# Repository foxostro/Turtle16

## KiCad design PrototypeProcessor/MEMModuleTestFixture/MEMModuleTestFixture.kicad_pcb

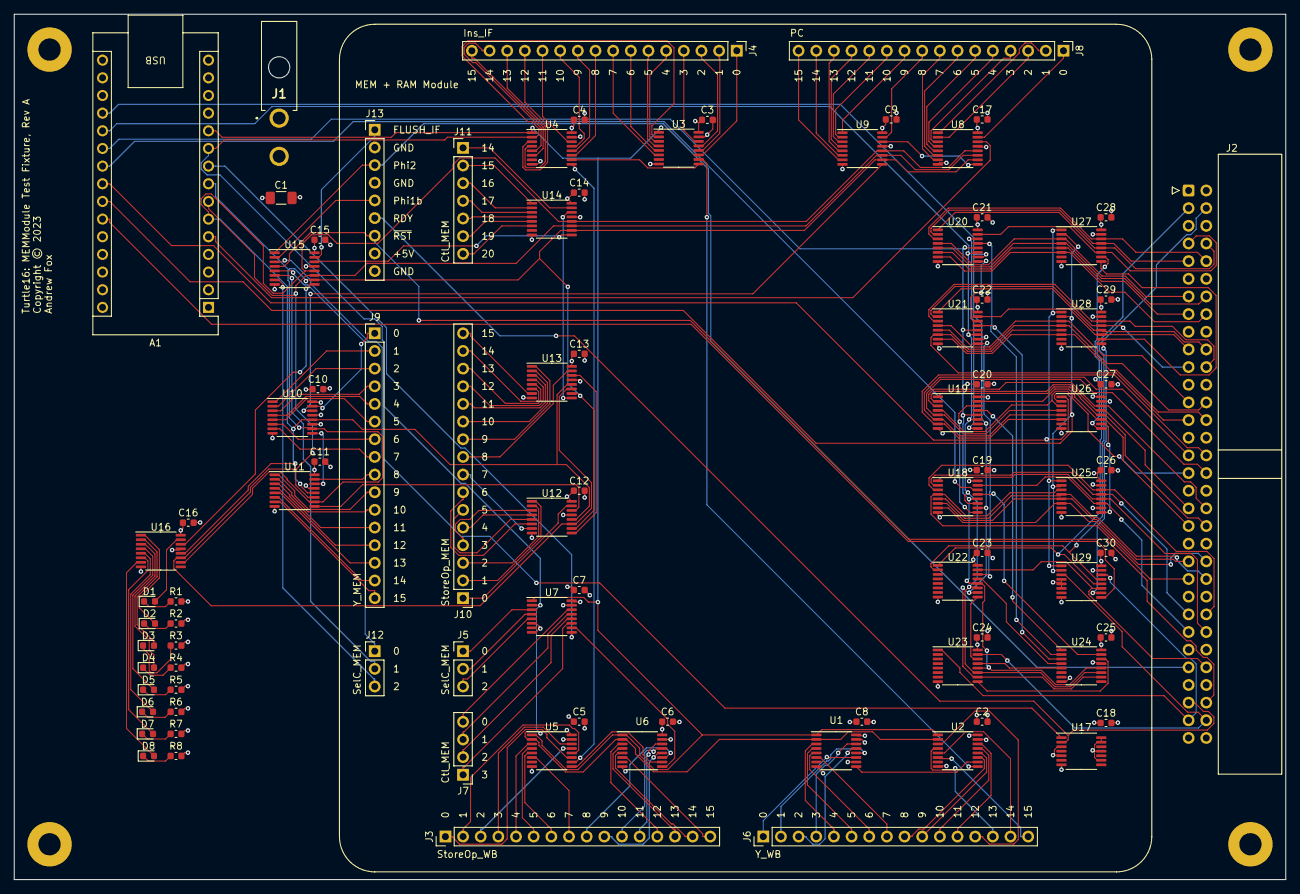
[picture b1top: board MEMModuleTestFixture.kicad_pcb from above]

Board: 4 copper layers, 182.9 x 124.5 mm, 93 parts (0 on the bottom side), 218 nets.

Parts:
A1: Arduino_Nano_Every; Arduino_Nano
C1: 100µF; C_1206_3216Metric_Pad1.33x1.80mm_HandSolder
C2, C3, C4, C5, C6, C7, C8, C9, C10, C11, C12, C13, C14, C15, C16, C17, C18, C19, C20, C21, C22, C23, C24, C25, C26, C27, C28, C29, C30: 0.1µF; C_0603_1608Metric
D1, D2, D3, D4, D5, D6, D7, D8: Red; LED_0603_1608Metric
H1, H2, H3, H4: MountingHole_Pad; MountingHole_3.2mm_M3_Pad
J1: Power; 172448-0002
J2: 71922-164LF; IDC-Header_2x32_P2.54mm_Horizontal
J3: StoreOp_WB; PinHeader_1x16_P2.54mm_Vertical
J4: Ins_IF; PinHeader_1x16_P2.54mm_Vertical
J5, J12: SelC_MEM; PinHeader_1x03_P2.54mm_Vertical
J6: Y_WB; PinHeader_1x16_P2.54mm_Vertical
J7: Ctl_MEM; PinHeader_1x04_P2.54mm_Vertical
J8: PC; PinHeader_1x16_P2.54mm_Vertical
J9: Y_MEM; PinHeader_1x16_P2.54mm_Vertical
J10: StoreOp_MEM; PinHeader_1x16_P2.54mm_Vertical
J11: Ctl_MEM; PinHeader_1x07_P2.54mm_Vertical
J13: Control Signals; PinHeader_1x09_P2.54mm_Vertical
R1, R2, R3, R4, R5, R6, R7, R8: 270R; C_0603_1608Metric
U1, U2, U3, U4, U5, U6, U7, U25, U26, U27, U28, U29: 74HC165; TSSOP-16_4.4x5mm_P0.65mm
U8, U9, U10, U11, U12, U13, U14, U15, U16, U18, U19, U20, U21, U22, U23, U24: 74HC595; TSSOP-16_4.4x5mm_P0.65mm
U17: 74HCT05; TSSOP-14_4.4x5mm_P0.65mm

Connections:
/Ctl_MEM14: J11.1, U14.15 (QA)
/Ctl_MEM15: J11.2, U14.1 (QB)
/Ctl_MEM16: J11.3, U14.2 (QC)
/Ctl_MEM17: J11.4, U14.3 (QD)
/Ctl_MEM18: J11.5, U14.4 (QE)
/Ctl_MEM19: J11.6, U14.5 (QF)
/Ctl_MEM20: J11.7, U14.6 (QG)
/Ctl_WB17: J7.1, U7.11 (D0)
/Ctl_WB18: J7.2, U7.12 (D1)
/Ctl_WB19: J7.3, U7.13 (D2)
/Ctl_WB20: J7.4, U7.14 (D3)
/Ins_IF0: J4.1, U3.11 (D0)
/Ins_IF1: J4.2, U3.12 (D1)
/Ins_IF2: J4.3, U3.13 (D2)
/Ins_IF3: J4.4, U3.14 (D3)
/Ins_IF4: J4.5, U3.3 (D4)
/Ins_IF5: J4.6, U3.4 (D5)
/Ins_IF6: J4.7, U3.5 (D6)
/Ins_IF7: J4.8, U3.6 (D7)
/Ins_IF8: J4.9, U4.11 (D0)
/Ins_IF9: J4.10, U4.12 (D1)
/Ins_IF10: J4.11, U4.13 (D2)
/Ins_IF11: J4.12, U4.14 (D3)
/Ins_IF12: J4.13, U4.3 (D4)
/Ins_IF13: J4.14, U4.4 (D5)
/Ins_IF14: J4.15, U4.5 (D6)
/Ins_IF15: J4.16, U4.6 (D7)
/MEM Prototype Inputs/FLUSH_IF: J13.1, U15.15 (QA)
/MEM Prototype Inputs/PC0: J8.1, U8.15 (QA)
/MEM Prototype Inputs/PC1: J8.2, U8.1 (QB)
/MEM Prototype Inputs/PC2: J8.3, U8.2 (QC)
/MEM Prototype Inputs/PC3: J8.4, U8.3 (QD)
/MEM Prototype Inputs/PC4: J8.5, U8.4 (QE)
/MEM Prototype Inputs/PC5: J8.6, U8.5 (QF)
/MEM Prototype Inputs/PC6: J8.7, U8.6 (QG)
/MEM Prototype Inputs/PC7: J8.8, U8.7 (QH)
/MEM Prototype Inputs/PC8: J8.9, U9.15 (QA)
/MEM Prototype Inputs/PC9: J8.10, U9.1 (QB)
/MEM Prototype Inputs/PC10: J8.11, U9.2 (QC)
/MEM Prototype Inputs/PC11: J8.12, U9.3 (QD)
/MEM Prototype Inputs/PC12: J8.13, U9.4 (QE)
/MEM Prototype Inputs/PC13: J8.14, U9.5 (QF)
/MEM Prototype Inputs/PC14: J8.15, U9.6 (QG)
/MEM Prototype Inputs/PC15: J8.16, U9.7 (QH)
/MEM Prototype Inputs/Phi1b: J13.5, U15.2 (QC)
/MEM Prototype Inputs/Phi2: J2.55, J13.3, U15.1 (QB)
/MEM Prototype Inputs/RDY: J2.59, J13.6, U17.2
/MEM Prototype Inputs/~RST_sync: J2.60, J13.7, U15.4 (QE)
/SelC_MEM0: J12.1, U15.5 (QF)
/SelC_MEM1: J12.2, U15.6 (QG)
/SelC_MEM2: J12.3, U15.7 (QH)
/SelC_WB0: J5.1, U7.3 (D4)
/SelC_WB1: J5.2, U7.4 (D5)
/SelC_WB2: J5.3, U7.5 (D6)
/StoreOp_MEM0: J10.1, U12.15 (QA)
/StoreOp_MEM1: J10.2, U12.1 (QB)
/StoreOp_MEM2: J10.3, U12.2 (QC)
/StoreOp_MEM3: J10.4, U12.3 (QD)
/StoreOp_MEM4: J10.5, U12.4 (QE)
/StoreOp_MEM5: J10.6, U12.5 (QF)
/StoreOp_MEM6: J10.7, U12.6 (QG)
/StoreOp_MEM7: J10.8, U12.7 (QH)
/StoreOp_MEM8: J10.9, U13.15 (QA)
/StoreOp_MEM9: J10.10, U13.1 (QB)
/StoreOp_MEM10: J10.11, U13.2 (QC)
/StoreOp_MEM11: J10.12, U13.3 (QD)
/StoreOp_MEM12: J10.13, U13.4 (QE)
/StoreOp_MEM13: J10.14, U13.5 (QF)
/StoreOp_MEM14: J10.15, U13.6 (QG)
/StoreOp_MEM15: J10.16, U13.7 (QH)
/StoreOp_WB0: J3.1, U5.11 (D0)
/StoreOp_WB1: J3.2, U5.12 (D1)
/StoreOp_WB2: J3.3, U5.13 (D2)
/StoreOp_WB3: J3.4, U5.14 (D3)
/StoreOp_WB4: J3.5, U5.3 (D4)
/StoreOp_WB5: J3.6, U5.4 (D5)
/StoreOp_WB6: J3.7, U5.5 (D6)
/StoreOp_WB7: J3.8, U5.6 (D7)
/StoreOp_WB8: J3.9, U6.11 (D0)
/StoreOp_WB9: J3.10, U6.12 (D1)
/StoreOp_WB10: J3.11, U6.13 (D2)
/StoreOp_WB11: J3.12, U6.14 (D3)
/StoreOp_WB12: J3.13, U6.3 (D4)
/StoreOp_WB13: J3.14, U6.4 (D5)
/StoreOp_WB14: J3.15, U6.5 (D6)
/StoreOp_WB15: J3.16, U6.6 (D7)
/System Bus Connector/Addr0: J2.7, U20.15 (QA), U27.11 (D0)
/System Bus Connector/Addr1: J2.8, U20.1 (QB), U27.12 (D1)
/System Bus Connector/Addr2: J2.9, U20.2 (QC), U27.13 (D2)
/System Bus Connector/Addr3: J2.10, U20.3 (QD), U27.14 (D3)
/System Bus Connector/Addr4: J2.13, U20.4 (QE), U27.3 (D4)
/System Bus Connector/Addr5: J2.14, U20.5 (QF), U27.4 (D5)
/System Bus Connector/Addr6: J2.15, U20.6 (QG), U27.5 (D6)
/System Bus Connector/Addr7: J2.16, U20.7 (QH), U27.6 (D7)
/System Bus Connector/Addr8: J2.19, U21.15 (QA), U28.11 (D0)
/System Bus Connector/Addr9: J2.20, U21.1 (QB), U28.12 (D1)
/System Bus Connector/Addr10: J2.21, U21.2 (QC), U28.13 (D2)
/System Bus Connector/Addr11: J2.22, U21.3 (QD), U28.14 (D3)
/System Bus Connector/Addr12: J2.25, U21.4 (QE), U28.3 (D4)
/System Bus Connector/Addr13: J2.26, U21.5 (QF), U28.4 (D5)
/System Bus Connector/Addr14: J2.27, U21.6 (QG), U28.5 (D6)
/System Bus Connector/Addr15: J2.28, U21.7 (QH), U28.6 (D7)
/System Bus Connector/Bank0: J2.56, U22.15 (QA), U29.11 (D0)
/System Bus Connector/Bank1: J2.3, U22.1 (QB), U29.12 (D1)
/System Bus Connector/Bank2: J2.4, U22.2 (QC), U29.13 (D2)
/System Bus Connector/IO0: J2.51, U18.15 (QA), U25.11 (D0)
/System Bus Connector/IO1: J2.52, U18.1 (QB), U25.12 (D1)
/System Bus Connector/IO2: J2.49, U18.2 (QC), U25.13 (D2)
/System Bus Connector/IO3: J2.50, U18.3 (QD), U25.14 (D3)
/System Bus Connector/IO4: J2.45, U18.4 (QE), U25.3 (D4)
/System Bus Connector/IO5: J2.46, U18.5 (QF), U25.4 (D5)
/System Bus Connector/IO6: J2.43, U18.6 (QG), U25.5 (D6)
/System Bus Connector/IO7: J2.44, U18.7 (QH), U25.6 (D7)
/System Bus Connector/IO8: J2.39, U19.15 (QA), U26.11 (D0)
/System Bus Connector/IO9: J2.40, U19.1 (QB), U26.12 (D1)
/System Bus Connector/IO10: J2.37, U19.2 (QC), U26.13 (D2)
/System Bus Connector/IO11: J2.38, U19.3 (QD), U26.14 (D3)
/System Bus Connector/IO12: J2.33, U19.4 (QE), U26.3 (D4)
/System Bus Connector/IO13: J2.34, U19.5 (QF), U26.4 (D5)
/System Bus Connector/IO14: J2.31, U19.6 (QG), U26.5 (D6)
/System Bus Connector/IO15: J2.32, U19.7 (QH), U26.6 (D7)
/System Bus Connector/~MemLoad: J2.62, U23.15 (QA), U29.3 (D4)
/System Bus Connector/~MemStore: J2.61, U23.1 (QB), U29.14 (D3)
/System Memory Bus Input/SCK: A1.24 (SCL/A5), U25.2 (CP), U26.2 (CP), U27.2 (CP), U28.2 (CP), U29.2 (CP)
/System Memory Bus Input/SO: A1.25 (A6), U29.9 (Q7)
/System Memory Bus Input/~PL: A1.23 (SDA/A4), U25.1 (~PL), U26.1 (~PL), U27.1 (~PL), U28.1 (~PL), U29.1 (~PL)
/System Memory Bus Output/OE0: U18.13 (~OE), U24.15 (QA)
/System Memory Bus Output/OE1: U19.13 (~OE), U24.1 (QB)
/System Memory Bus Output/OE2: U20.13 (~OE), U24.2 (QC)
/System Memory Bus Output/OE3: U21.13 (~OE), U24.3 (QD)
/System Memory Bus Output/OE4: U22.13 (~OE), U24.4 (QE)
/System Memory Bus Output/OE5: U23.13 (~OE), U24.5 (QF)
/System Memory Bus Output/RCLK: A1.21 (A2), U18.12 (RCLK), U19.12 (RCLK), U20.12 (RCLK), U21.12 (RCLK), U22.12 (RCLK), U23.12 (RCLK), U24.12 (RCLK)
/System Memory Bus Output/SCK: A1.20 (A1), U18.11 (SRCLK), U19.11 (SRCLK), U20.11 (SRCLK), U21.11 (SRCLK), U22.11 (SRCLK), U23.11 (SRCLK), U24.11 (SRCLK)
/System Memory Bus Output/SI: A1.22 (A3), U18.14 (SER)
/System Memory Bus Output/~CLR: A1.19 (A0), U18.10 (~SRCLR), U19.10 (~SRCLR), U20.10 (~SRCLR), U21.10 (~SRCLR), U22.10 (~SRCLR), U23.10 (~SRCLR), U24.10 (~SRCLR)
/Test Fixture Inputs/SCK: A1.10 (D7), U1.2 (CP), U2.2 (CP), U3.2 (CP), U4.2 (CP), U5.2 (CP), U6.2 (CP), U7.2 (CP)
/Test Fixture Inputs/SO: A1.9 (D6), U7.9 (Q7)
/Test Fixture Inputs/~PL: A1.11 (D8), U1.1 (~PL), U2.1 (~PL), U3.1 (~PL), U4.1 (~PL), U5.1 (~PL), U6.1 (~PL), U7.1 (~PL)
/Test Fixture Outputs/RCLK: A1.6 (D3), U8.12 (RCLK), U9.12 (RCLK), U10.12 (RCLK), U11.12 (RCLK), U12.12 (RCLK), U13.12 (RCLK), U14.12 (RCLK), U15.12 (RCLK), U16.12 (RCLK)
/Test Fixture Outputs/SCK: A1.7 (D4), U8.11 (SRCLK), U9.11 (SRCLK), U10.11 (SRCLK), U11.11 (SRCLK), U12.11 (SRCLK), U13.11 (SRCLK), U14.11 (SRCLK), U15.11 (SRCLK), U16.11 (SRCLK)
/Test Fixture Outputs/SI: A1.5 (D2), U8.14 (SER)
/Test Fixture Outputs/~CLR: A1.8 (D5), U8.10 (~SRCLR), U9.10 (~SRCLR), U10.10 (~SRCLR), U11.10 (~SRCLR), U12.10 (~SRCLR), U13.10 (~SRCLR), U14.10 (~SRCLR), U15.10 (~SRCLR), U16.10 (~SRCLR)
/Y_MEM0: J9.1, U10.15 (QA)
/Y_MEM1: J9.2, U10.1 (QB)
/Y_MEM2: J9.3, U10.2 (QC)
/Y_MEM3: J9.4, U10.3 (QD)
/Y_MEM4: J9.5, U10.4 (QE)
/Y_MEM5: J9.6, U10.5 (QF)
/Y_MEM6: J9.7, U10.6 (QG)
/Y_MEM7: J9.8, U10.7 (QH)
/Y_MEM8: J9.9, U11.15 (QA)
/Y_MEM9: J9.10, U11.1 (QB)
/Y_MEM10: J9.11, U11.2 (QC)
/Y_MEM11: J9.12, U11.3 (QD)
/Y_MEM12: J9.13, U11.4 (QE)
/Y_MEM13: J9.14, U11.5 (QF)
/Y_MEM14: J9.15, U11.6 (QG)
/Y_MEM15: J9.16, U11.7 (QH)
/Y_WB0: J6.1, U1.11 (D0)
/Y_WB1: J6.2, U1.12 (D1)
/Y_WB2: J6.3, U1.13 (D2)
/Y_WB3: J6.4, U1.14 (D3)
/Y_WB4: J6.5, U1.3 (D4)
/Y_WB5: J6.6, U1.4 (D5)
/Y_WB6: J6.7, U1.5 (D6)
/Y_WB7: J6.8, U1.6 (D7)
/Y_WB8: J6.9, U2.11 (D0)
/Y_WB9: J6.10, U2.12 (D1)
/Y_WB10: J6.11, U2.13 (D2)
/Y_WB11: J6.12, U2.14 (D3)
/Y_WB12: J6.13, U2.3 (D4)
/Y_WB13: J6.14, U2.4 (D5)
/Y_WB14: J6.15, U2.5 (D6)
/Y_WB15: J6.16, U2.6 (D7)
GND: A1.4 (GND), A1.29 (GND), C1.2, C2.2, C3.2, C4.2, C5.2, C6.2, C7.2, C8.2, C9.2, C10.2, C11.2, C12.2, C13.2, C14.2, C15.2, C16.2, C17.2, C18.2, C19.2, C20.2, C21.2, C22.2, C23.2, C24.2, C25.2, C26.2, C27.2, C28.2, C29.2, C30.2, H1.1, H2.1, H3.1, H4.1, J1.2, J2.1, J2.2, J2.5, J2.6, J2.11, J2.12, J2.17, J2.18, J2.23, J2.24, J2.29, J2.30, J2.35, J2.36, J2.41, J2.42, J2.47, J2.48, J2.53, J2.54, J2.57, J2.58, J13.2, J13.4, J13.9, R1.2, R2.2, R3.2, R4.2, R5.2, R6.2, R7.2, R8.2, U1.8 (GND), U1.10 (DS), U1.15 (~CE), U2.8 (GND), U2.15 (~CE), U3.8 (GND), U3.15 (~CE), U4.8 (GND), U4.15 (~CE), U5.8 (GND), U5.15 (~CE), U6.8 (GND), U6.15 (~CE), U7.6 (D7), U7.8 (GND), U7.15 (~CE), U8.8 (GND), U8.13 (~OE), U9.8 (GND), U9.13 (~OE), U10.8 (GND), U10.13 (~OE), U11.8 (GND), U11.13 (~OE), U12.8 (GND), U12.13 (~OE), U13.8 (GND), U13.13 (~OE), U14.8 (GND), U14.13 (~OE), U15.8 (GND), U15.13 (~OE), U16.8 (GND), U16.13 (~OE), U17.7 (GND), U18.8 (GND), U19.8 (GND), U20.8 (GND), U21.8 (GND), U22.8 (GND), U23.8 (GND), U24.8 (GND), U24.13 (~OE), U25.8 (GND), U25.10 (DS), U25.15 (~CE), U26.8 (GND), U26.15 (~CE), U27.8 (GND), U27.15 (~CE), U28.8 (GND), U28.15 (~CE), U29.4 (D5), U29.5 (D6), U29.6 (D7), U29.8 (GND), U29.15 (~CE)
unnamed: D1.2 (A), U16.15 (QA)
unnamed: D1.1 (K), R1.1
unnamed: D2.2 (A), U16.1 (QB)
unnamed: D2.1 (K), R2.1
unnamed: D3.2 (A), U16.2 (QC)
unnamed: D3.1 (K), R3.1
unnamed: D4.2 (A), U16.3 (QD)
unnamed: D4.1 (K), R4.1
unnamed: D5.2 (A), U16.4 (QE)
unnamed: D5.1 (K), R5.1
unnamed: D6.2 (A), U16.5 (QF)
unnamed: D6.1 (K), R6.1
unnamed: D7.2 (A), U16.6 (QG)
unnamed: D7.1 (K), R7.1
unnamed: D8.2 (A), U16.7 (QH)
unnamed: D8.1 (K), R8.1
unnamed: U1.9 (Q7), U2.10 (DS)
unnamed: U2.9 (Q7), U3.10 (DS)
unnamed: U3.9 (Q7), U4.10 (DS)
unnamed: U4.9 (Q7), U5.10 (DS)
unnamed: U5.9 (Q7), U6.10 (DS)
unnamed: U6.9 (Q7), U7.10 (DS)
unnamed: U8.9 (QH'), U9.14 (SER)
unnamed: U10.9 (QH'), U11.14 (SER)
unnamed: U9.9 (QH'), U10.14 (SER)
unnamed: U11.9 (QH'), U12.14 (SER)
unnamed: U12.9 (QH'), U13.14 (SER)
unnamed: U13.9 (QH'), U14.14 (SER)
unnamed: U14.9 (QH'), U15.14 (SER)
unnamed: U15.3 (QD), U17.1
unnamed: U15.9 (QH'), U16.14 (SER)
unnamed: U18.9 (QH'), U19.14 (SER)
unnamed: U19.9 (QH'), U20.14 (SER)
unnamed: U20.9 (QH'), U21.14 (SER)
unnamed: U21.9 (QH'), U22.14 (SER)
unnamed: U22.9 (QH'), U23.14 (SER)
unnamed: U23.9 (QH'), U24.14 (SER)
unnamed: U25.9 (Q7), U26.10 (DS)
unnamed: U26.9 (Q7), U27.10 (DS)
unnamed: U27.9 (Q7), U28.10 (DS)
unnamed: U28.9 (Q7), U29.10 (DS)
VCC: A1.3 (~RESET), A1.28 (~RESET), A1.30 (VIN), C1.1, C2.1, C3.1, C4.1, C5.1, C6.1, C7.1, C8.1, C9.1, C10.1, C11.1, C12.1, C13.1, C14.1, C15.1, C16.1, C17.1, C18.1, C19.1, C20.1, C21.1, C22.1, C23.1, C24.1, C25.1, C26.1, C27.1, C28.1, C29.1, C30.1, J1.1, J2.63, J2.64, J13.8, U1.16 (VCC), U2.16 (VCC), U3.16 (VCC), U4.16 (VCC), U5.16 (VCC), U6.16 (VCC), U7.16 (VCC), U8.16 (VCC), U9.16 (VCC), U10.16 (VCC), U11.16 (VCC), U12.16 (VCC), U13.16 (VCC), U14.16 (VCC), U15.16 (VCC), U16.16 (VCC), U17.3, U17.5, U17.9, U17.11, U17.13, U17.14 (VCC), U18.16 (VCC), U19.16 (VCC), U20.16 (VCC), U21.16 (VCC), U22.16 (VCC), U23.16 (VCC), U24.16 (VCC), U25.16 (VCC), U26.16 (VCC), U27.16 (VCC), U28.16 (VCC), U29.16 (VCC)

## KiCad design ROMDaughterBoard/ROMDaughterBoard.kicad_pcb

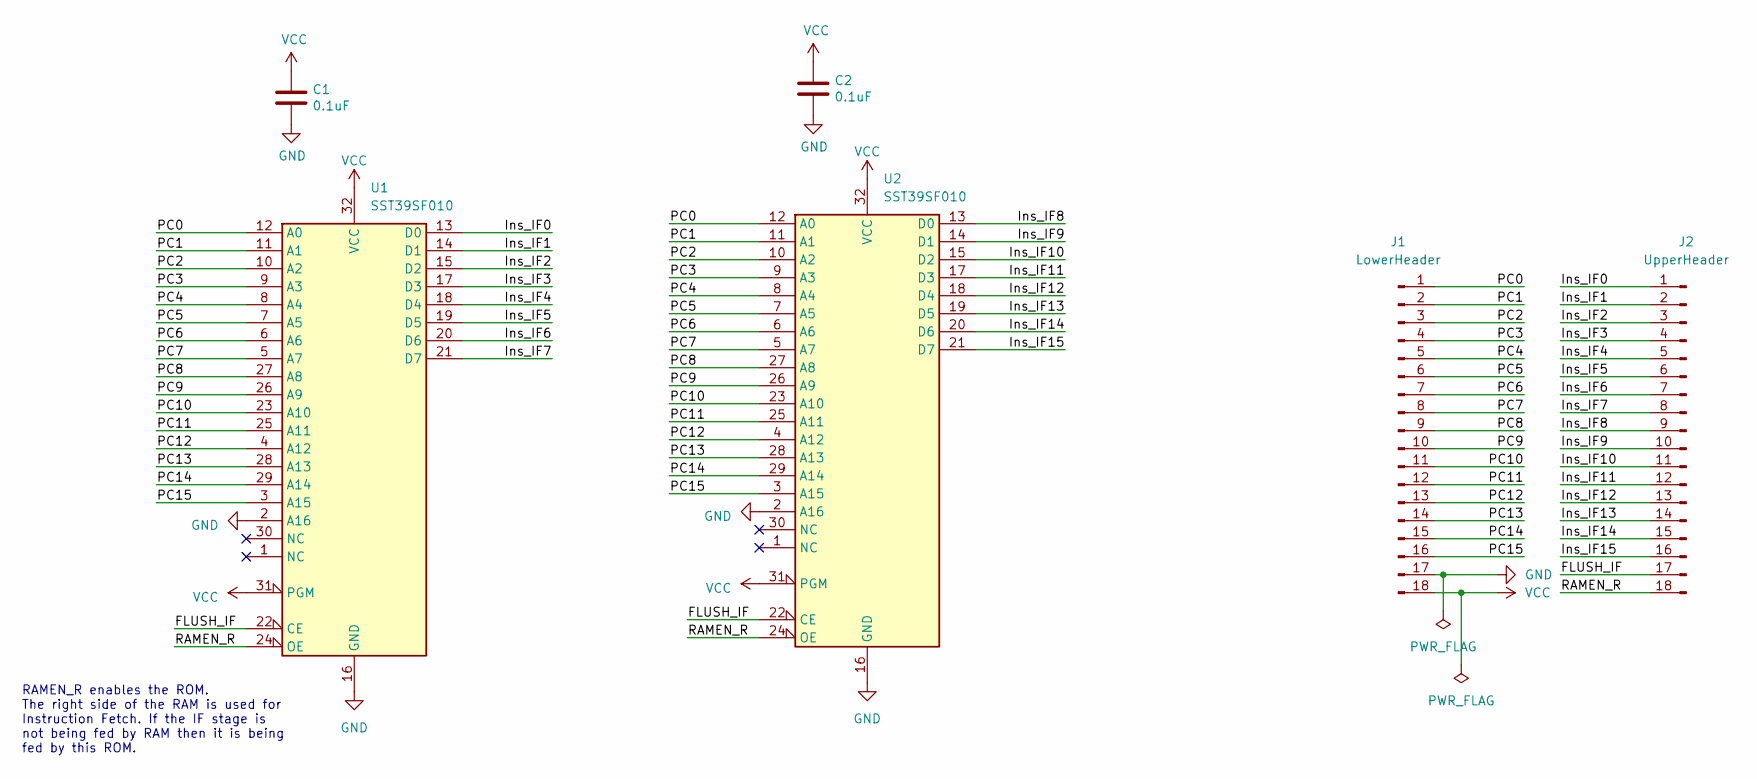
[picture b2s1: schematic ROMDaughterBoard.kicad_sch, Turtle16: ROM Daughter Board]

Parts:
C1, C2: 0.1uF; C_0603_1608Metric; Manufacturer# EMK107B7104KAHT; Mouser# 963-EMK107B7104KAHT
J1: LowerHeader; PinHeader_1x18_P2.54mm_Vertical
J2: UpperHeader; PinHeader_1x18_P2.54mm_Vertical
U1, U2: SST39SF010; 843221B1RKTP; Manufacturer# 8432-21B1-RK-TP; Mouser# 517-8432-21B1-RK-TP

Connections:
/FLUSH_IF: J2.17, U1.22 (CE), U2.22 (CE)
/Ins_IF0: J2.1, U1.13 (D0)
/Ins_IF1: J2.2, U1.14 (D1)
/Ins_IF2: J2.3, U1.15 (D2)
/Ins_IF3: J2.4, U1.17 (D3)
/Ins_IF4: J2.5, U1.18 (D4)
/Ins_IF5: J2.6, U1.19 (D5)
/Ins_IF6: J2.7, U1.20 (D6)
/Ins_IF7: J2.8, U1.21 (D7)
/Ins_IF8: J2.9, U2.13 (D0)
/Ins_IF9: J2.10, U2.14 (D1)
/Ins_IF10: J2.11, U2.15 (D2)
/Ins_IF11: J2.12, U2.17 (D3)
/Ins_IF12: J2.13, U2.18 (D4)
/Ins_IF13: J2.14, U2.19 (D5)
/Ins_IF14: J2.15, U2.20 (D6)
/Ins_IF15: J2.16, U2.21 (D7)
/PC0: J1.1, U1.12 (A0), U2.12 (A0)
/PC1: J1.2, U1.11 (A1), U2.11 (A1)
/PC2: J1.3, U1.10 (A2), U2.10 (A2)
/PC3: J1.4, U1.9 (A3), U2.9 (A3)
/PC4: J1.5, U1.8 (A4), U2.8 (A4)
/PC5: J1.6, U1.7 (A5), U2.7 (A5)
/PC6: J1.7, U1.6 (A6), U2.6 (A6)
/PC7: J1.8, U1.5 (A7), U2.5 (A7)
/PC8: J1.9, U1.27 (A8), U2.27 (A8)
/PC9: J1.10, U1.26 (A9), U2.26 (A9)
/PC10: J1.11, U1.23 (A10), U2.23 (A10)
/PC11: J1.12, U1.25 (A11), U2.25 (A11)
/PC12: J1.13, U1.4 (A12), U2.4 (A12)
/PC13: J1.14, U1.28 (A13), U2.28 (A13)
/PC14: J1.15, U1.29 (A14), U2.29 (A14)
/PC15: J1.16, U1.3 (A15), U2.3 (A15)
/RAMEN_R: J2.18, U1.24 (OE), U2.24 (OE)
GND: C1.2, C2.2, J1.17, U1.2 (A16), U1.16 (GND), U2.2 (A16), U2.16 (GND)
VCC: C1.1, C2.1, J1.18, U1.31 (PGM), U1.32 (VCC), U2.31 (PGM), U2.32 (VCC)

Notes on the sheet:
RAMEN_R enables the ROM. The right side of the RAM is used for Instruction Fetch. If the IF stage is not being fed by RAM then it is being fed by this ROM.

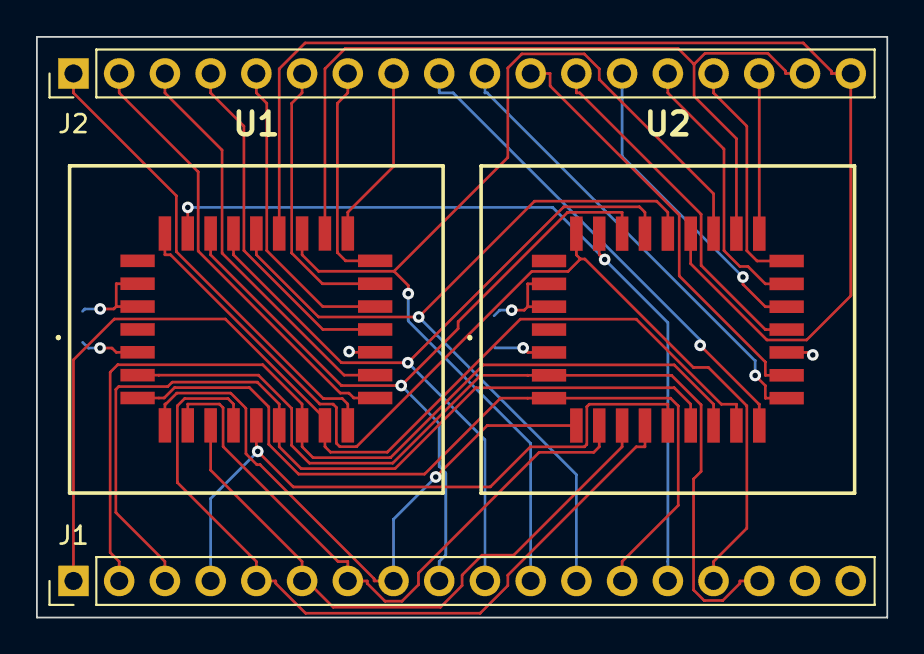
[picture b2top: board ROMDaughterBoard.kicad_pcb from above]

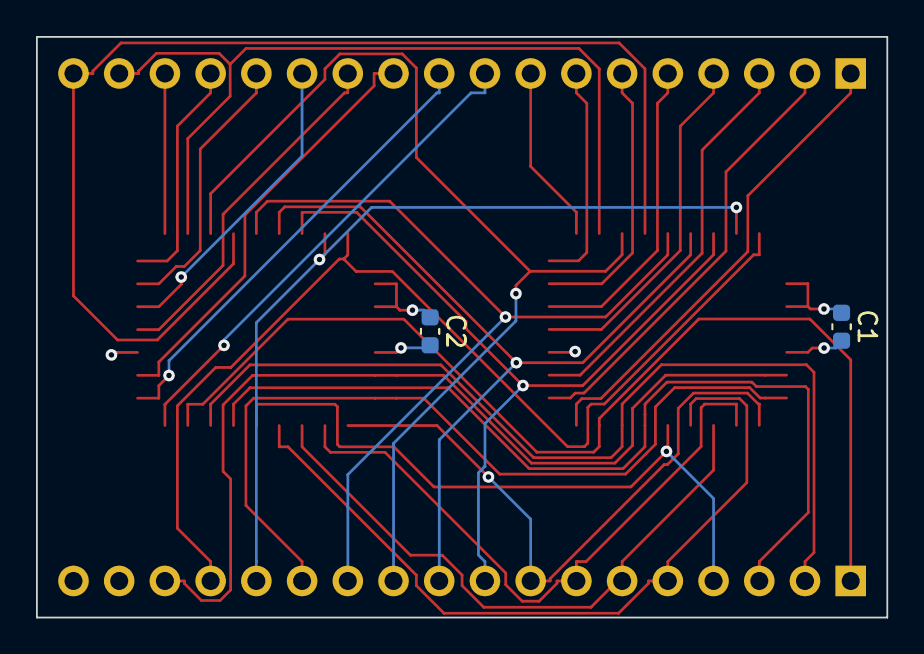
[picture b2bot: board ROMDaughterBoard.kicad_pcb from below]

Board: 4 copper layers, 47.2 x 32.3 mm, 6 parts (2 on the bottom side), 36 nets.

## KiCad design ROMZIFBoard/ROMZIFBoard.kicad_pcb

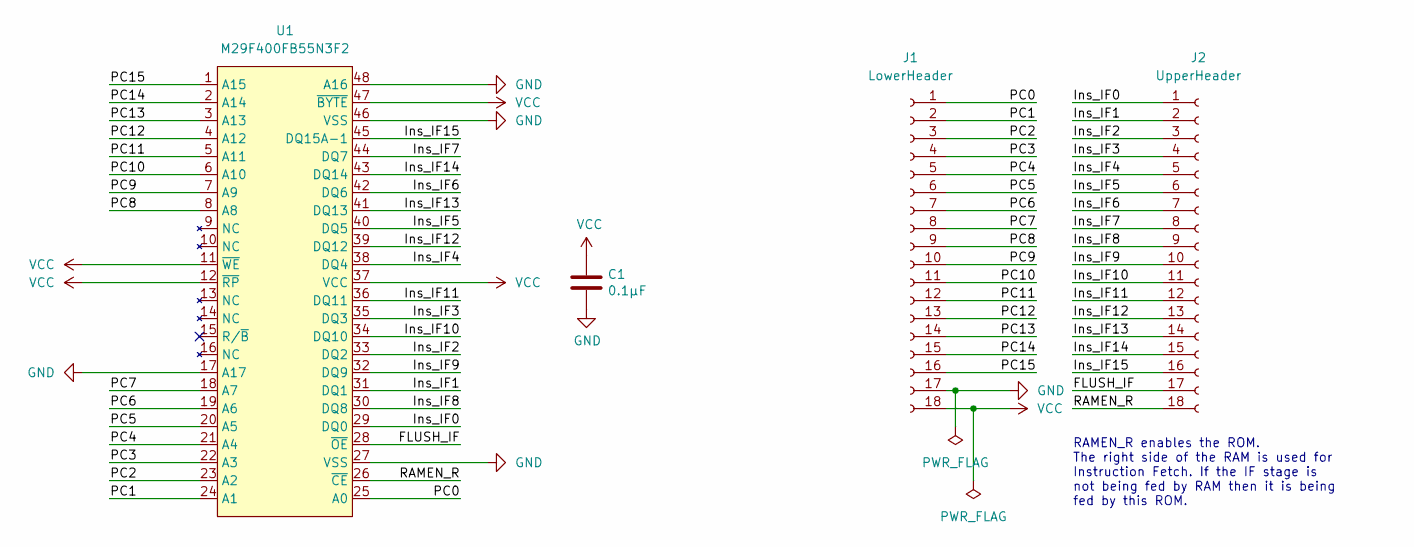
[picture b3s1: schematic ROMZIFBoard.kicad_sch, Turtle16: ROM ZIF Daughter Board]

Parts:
C1: 0.1μF; C_0603_1608Metric_Pad1.08x0.95mm_HandSolder
J1: LowerHeader; PinSocket_1x18_P2.54mm_Vertical
J2: UpperHeader; PinSocket_1x18_P2.54mm_Vertical
U1: M29F400FB55N3F2; DIP-48_W15.24mm_Socket

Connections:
/FLUSH_IF: J2.17, U1.28 (~OE)
/Ins_IF0: J2.1, U1.29 (DQ0)
/Ins_IF1: J2.2, U1.31 (DQ1)
/Ins_IF2: J2.3, U1.33 (DQ2)
/Ins_IF3: J2.4, U1.35 (DQ3)
/Ins_IF4: J2.5, U1.38 (DQ4)
/Ins_IF5: J2.6, U1.40 (DQ5)
/Ins_IF6: J2.7, U1.42 (DQ6)
/Ins_IF7: J2.8, U1.44 (DQ7)
/Ins_IF8: J2.9, U1.30 (DQ8)
/Ins_IF9: J2.10, U1.32 (DQ9)
/Ins_IF10: J2.11, U1.34 (DQ10)
/Ins_IF11: J2.12, U1.36 (DQ11)
/Ins_IF12: J2.13, U1.39 (DQ12)
/Ins_IF13: J2.14, U1.41 (DQ13)
/Ins_IF14: J2.15, U1.43 (DQ14)
/Ins_IF15: J2.16, U1.45 (DQ15A-1)
/PC0: J1.1, U1.25 (A0)
/PC1: J1.2, U1.24 (A1)
/PC2: J1.3, U1.23 (A2)
/PC3: J1.4, U1.22 (A3)
/PC4: J1.5, U1.21 (A4)
/PC5: J1.6, U1.20 (A5)
/PC6: J1.7, U1.19 (A6)
/PC7: J1.8, U1.18 (A7)
/PC8: J1.9, U1.8 (A8)
/PC9: J1.10, U1.7 (A9)
/PC10: J1.11, U1.6 (A10)
/PC11: J1.12, U1.5 (A11)
/PC12: J1.13, U1.4 (A12)
/PC13: J1.14, U1.3 (A13)
/PC14: J1.15, U1.2 (A14)
/PC15: J1.16, U1.1 (A15)
/RAMEN_R: J2.18, U1.26 (~CE)
GND: C1.2, J1.17, U1.17 (A17), U1.27 (VSS), U1.46 (VSS), U1.48 (A16)
VCC: C1.1, J1.18, U1.11 (~WE), U1.12 (~RP), U1.37 (VCC), U1.47 (~BYTE)

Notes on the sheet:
RAMEN_R enables the ROM. The right side of the RAM is used for Instruction Fetch. If the IF stage is not being fed by RAM then it is being fed by this ROM.

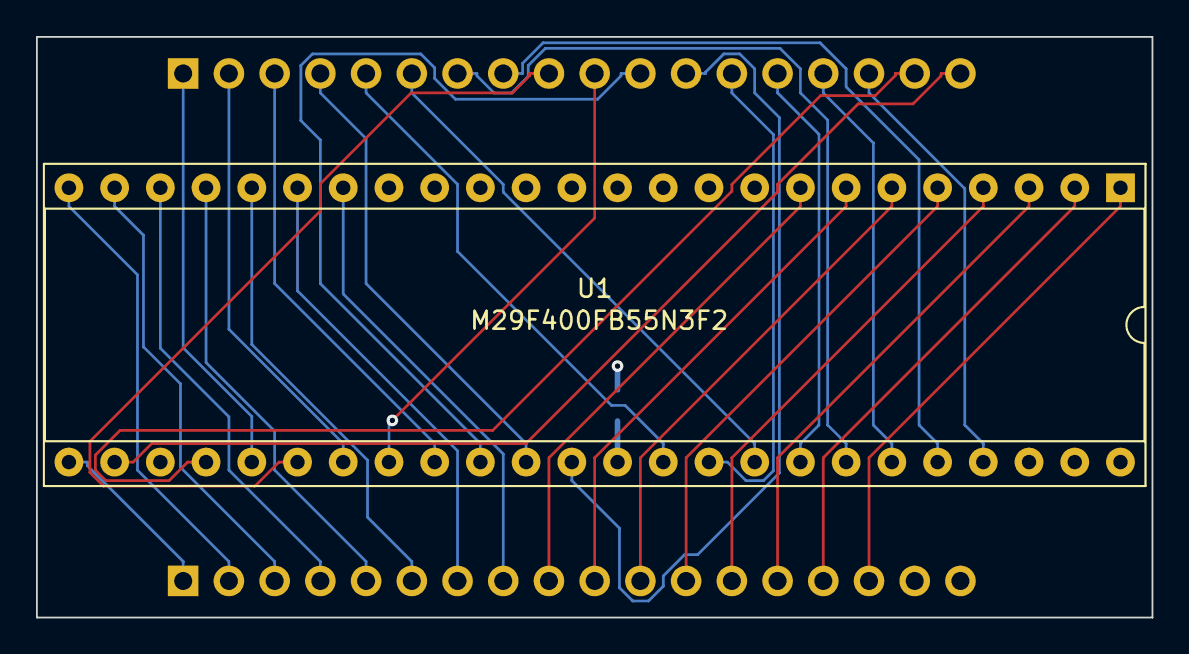
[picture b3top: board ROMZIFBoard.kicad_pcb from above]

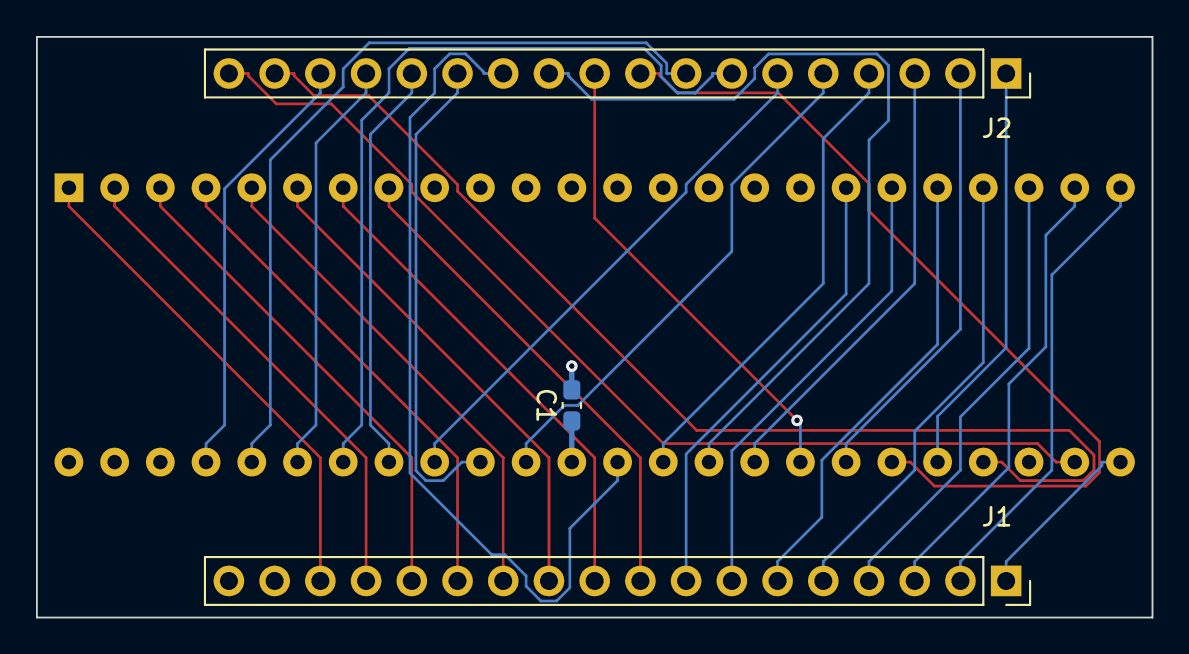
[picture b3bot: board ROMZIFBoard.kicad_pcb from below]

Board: 4 copper layers, 62.0 x 32.3 mm, 4 parts (3 on the bottom side), 36 nets.

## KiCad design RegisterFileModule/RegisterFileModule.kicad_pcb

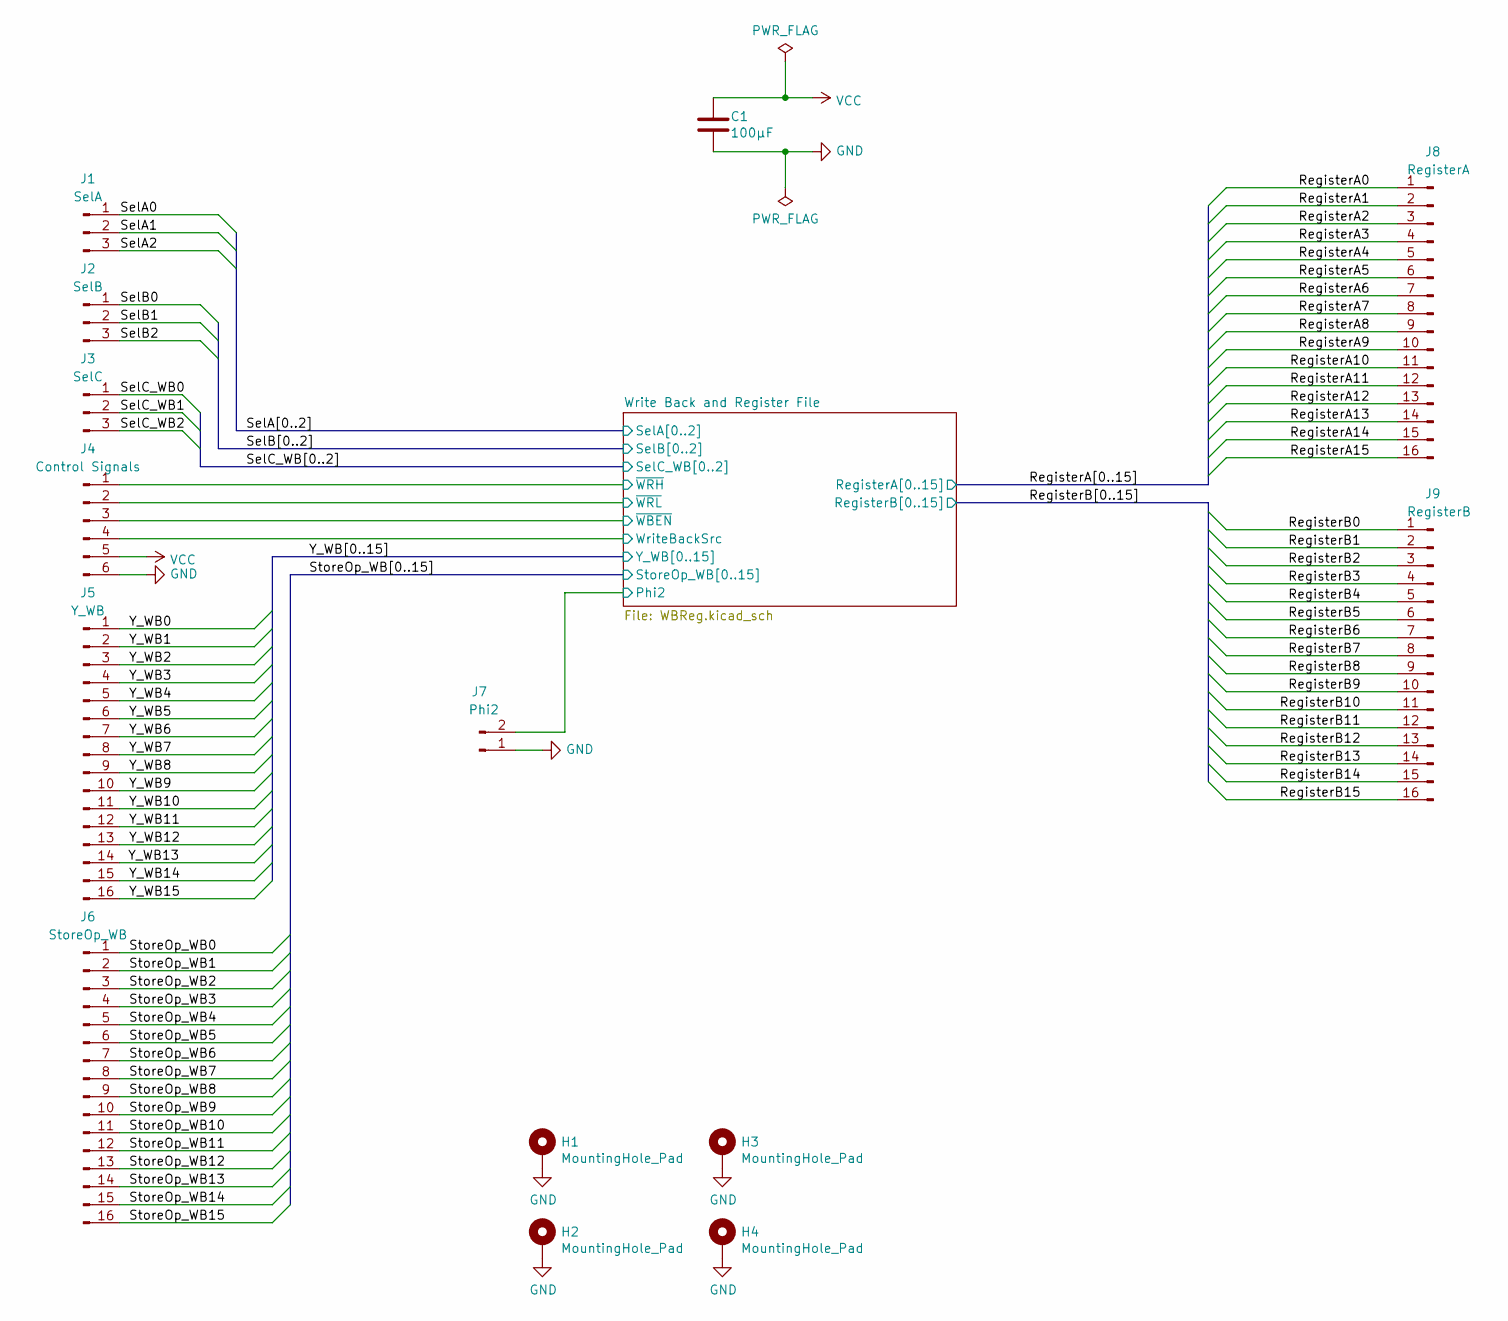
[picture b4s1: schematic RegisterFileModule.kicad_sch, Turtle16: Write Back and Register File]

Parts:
C1: 100µF; C_1206_3216Metric_Pad1.33x1.80mm_HandSolder
H1, H2, H3, H4: MountingHole_Pad; MountingHole_3.2mm_M3_Pad
J1: SelA; PinHeader_1x03_P2.54mm_Vertical
J2: SelB; PinHeader_1x03_P2.54mm_Vertical
J3: SelC; PinHeader_1x03_P2.54mm_Vertical
J4: Control Signals; PinHeader_1x06_P2.54mm_Vertical
J5: Y_WB; PinHeader_1x16_P2.54mm_Vertical
J6: StoreOp_WB; PinHeader_1x16_P2.54mm_Vertical
J7: Phi2; PinHeader_1x02_P2.54mm_Vertical
J8: RegisterA; PinHeader_1x16_P2.54mm_Vertical
J9: RegisterB; PinHeader_1x16_P2.54mm_Vertical

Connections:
/RegisterA0: J8.1; also elsewhere on the board
/RegisterA1: J8.2; also elsewhere on the board
/RegisterA2: J8.3; also elsewhere on the board
/RegisterA3: J8.4; also elsewhere on the board
/RegisterA4: J8.5; also elsewhere on the board
/RegisterA5: J8.6; also elsewhere on the board
/RegisterA6: J8.7; also elsewhere on the board
/RegisterA7: J8.8; also elsewhere on the board
/RegisterA8: J8.9; also elsewhere on the board
/RegisterA9: J8.10; also elsewhere on the board
/RegisterA10: J8.11; also elsewhere on the board
/RegisterA11: J8.12; also elsewhere on the board
/RegisterA12: J8.13; also elsewhere on the board
/RegisterA13: J8.14; also elsewhere on the board
/RegisterA14: J8.15; also elsewhere on the board
/RegisterA15: J8.16; also elsewhere on the board
/RegisterB0: J9.1; also elsewhere on the board
/RegisterB1: J9.2; also elsewhere on the board
/RegisterB2: J9.3; also elsewhere on the board
/RegisterB3: J9.4; also elsewhere on the board
/RegisterB4: J9.5; also elsewhere on the board
/RegisterB5: J9.6; also elsewhere on the board
/RegisterB6: J9.7; also elsewhere on the board
/RegisterB7: J9.8; also elsewhere on the board
/RegisterB8: J9.9; also elsewhere on the board
/RegisterB9: J9.10; also elsewhere on the board
/RegisterB10: J9.11; also elsewhere on the board
/RegisterB11: J9.12; also elsewhere on the board
/RegisterB12: J9.13; also elsewhere on the board
/RegisterB13: J9.14; also elsewhere on the board
/RegisterB14: J9.15; also elsewhere on the board
/RegisterB15: J9.16; also elsewhere on the board
/SelA0: J1.1; also elsewhere on the board
/SelA1: J1.2; also elsewhere on the board
/SelA2: J1.3; also elsewhere on the board
/SelB0: J2.1; also elsewhere on the board
/SelB1: J2.2; also elsewhere on the board
/SelB2: J2.3; also elsewhere on the board
/SelC_WB0: J3.1; also elsewhere on the board
/SelC_WB1: J3.2; also elsewhere on the board
/SelC_WB2: J3.3; also elsewhere on the board
/StoreOp_WB0: J6.1; also elsewhere on the board
/StoreOp_WB1: J6.2; also elsewhere on the board
/StoreOp_WB2: J6.3; also elsewhere on the board
/StoreOp_WB3: J6.4; also elsewhere on the board
/StoreOp_WB4: J6.5; also elsewhere on the board
/StoreOp_WB5: J6.6; also elsewhere on the board
/StoreOp_WB6: J6.7; also elsewhere on the board
/StoreOp_WB7: J6.8; also elsewhere on the board
/StoreOp_WB8: J6.9; also elsewhere on the board
/StoreOp_WB9: J6.10; also elsewhere on the board
/StoreOp_WB10: J6.11; also elsewhere on the board
/StoreOp_WB11: J6.12; also elsewhere on the board
/StoreOp_WB12: J6.13; also elsewhere on the board
/StoreOp_WB13: J6.14; also elsewhere on the board
/StoreOp_WB14: J6.15; also elsewhere on the board
/StoreOp_WB15: J6.16; also elsewhere on the board
/Write Back and Register File/Phi2: J7.2; also elsewhere on the board
/Write Back and Register File/WriteBackSrc: J4.4; also elsewhere on the board
/Write Back and Register File/~WBEN: J4.3; also elsewhere on the board
/Write Back and Register File/~WRH: J4.1; also elsewhere on the board
/Write Back and Register File/~WRL: J4.2; also elsewhere on the board
/Y_WB0: J5.1; also elsewhere on the board
/Y_WB1: J5.2; also elsewhere on the board
/Y_WB2: J5.3; also elsewhere on the board
/Y_WB3: J5.4; also elsewhere on the board
/Y_WB4: J5.5; also elsewhere on the board
/Y_WB5: J5.6; also elsewhere on the board
/Y_WB6: J5.7; also elsewhere on the board
/Y_WB7: J5.8; also elsewhere on the board
/Y_WB8: J5.9; also elsewhere on the board
/Y_WB9: J5.10; also elsewhere on the board
/Y_WB10: J5.11; also elsewhere on the board
/Y_WB11: J5.12; also elsewhere on the board
/Y_WB12: J5.13; also elsewhere on the board
/Y_WB13: J5.14; also elsewhere on the board
/Y_WB14: J5.15; also elsewhere on the board
/Y_WB15: J5.16; also elsewhere on the board
GND: C1.2, H1.1, H2.1, H3.1, H4.1, J4.6, J7.1; also elsewhere on the board
VCC: C1.1, J4.5; also elsewhere on the board

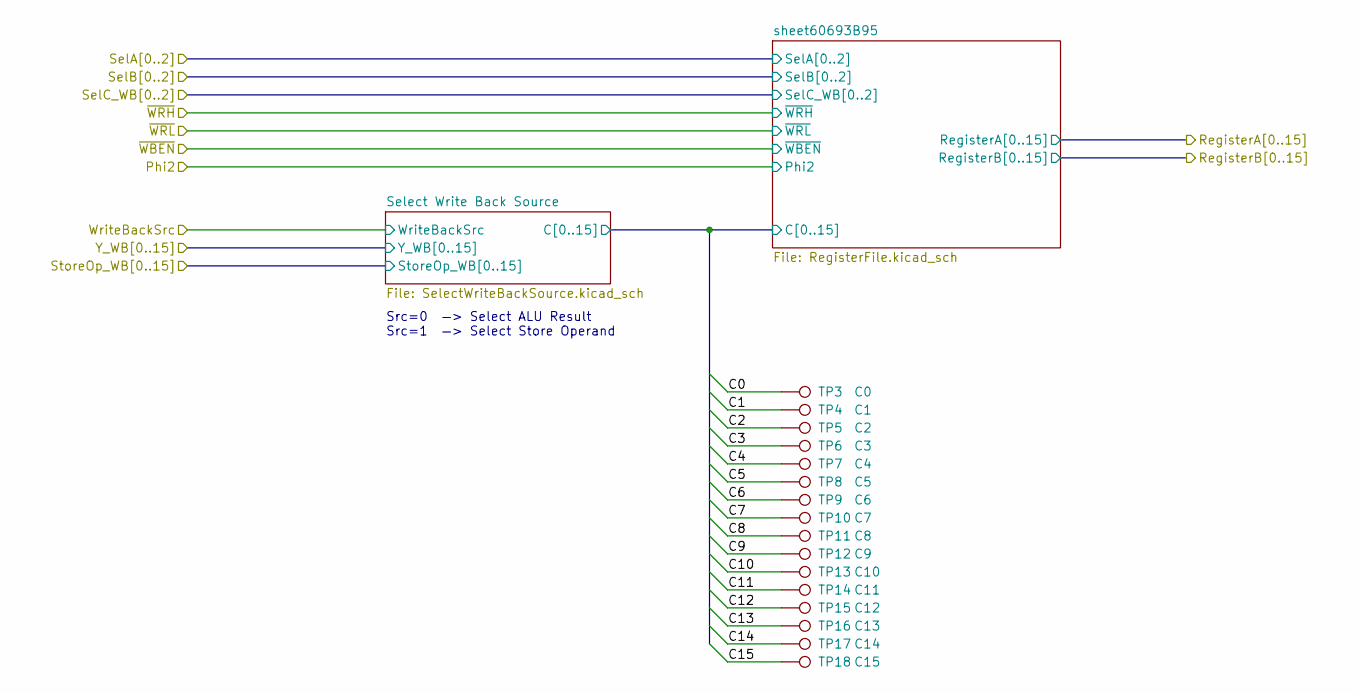
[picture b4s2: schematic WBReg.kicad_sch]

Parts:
TP3: C0; TestPoint_Pad_D1.0mm
TP4: C1; TestPoint_Pad_D1.0mm
TP5: C2; TestPoint_Pad_D1.0mm
TP6: C3; TestPoint_Pad_D1.0mm
TP7: C4; TestPoint_Pad_D1.0mm
TP8: C5; TestPoint_Pad_D1.0mm
TP9: C6; TestPoint_Pad_D1.0mm
TP10: C7; TestPoint_Pad_D1.0mm
TP11: C8; TestPoint_Pad_D1.0mm
TP12: C9; TestPoint_Pad_D1.0mm
TP13: C10; TestPoint_Pad_D1.0mm
TP14: C11; TestPoint_Pad_D1.0mm
TP15: C12; TestPoint_Pad_D1.0mm
TP16: C13; TestPoint_Pad_D1.0mm
TP17: C14; TestPoint_Pad_D1.0mm
TP18: C15; TestPoint_Pad_D1.0mm

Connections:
/Write Back and Register File/Select Write Back Source/C0: TP3.1; also elsewhere on the board
/Write Back and Register File/Select Write Back Source/C1: TP4.1; also elsewhere on the board
/Write Back and Register File/Select Write Back Source/C2: TP5.1; also elsewhere on the board
/Write Back and Register File/Select Write Back Source/C3: TP6.1; also elsewhere on the board
/Write Back and Register File/Select Write Back Source/C4: TP7.1; also elsewhere on the board
/Write Back and Register File/Select Write Back Source/C5: TP8.1; also elsewhere on the board
/Write Back and Register File/Select Write Back Source/C6: TP9.1; also elsewhere on the board
/Write Back and Register File/Select Write Back Source/C7: TP10.1; also elsewhere on the board
/Write Back and Register File/Select Write Back Source/C8: TP11.1; also elsewhere on the board
/Write Back and Register File/Select Write Back Source/C9: TP12.1; also elsewhere on the board
/Write Back and Register File/Select Write Back Source/C10: TP13.1; also elsewhere on the board
/Write Back and Register File/Select Write Back Source/C11: TP14.1; also elsewhere on the board
/Write Back and Register File/Select Write Back Source/C12: TP15.1; also elsewhere on the board
/Write Back and Register File/Select Write Back Source/C13: TP16.1; also elsewhere on the board
/Write Back and Register File/Select Write Back Source/C14: TP17.1; also elsewhere on the board
/Write Back and Register File/Select Write Back Source/C15: TP18.1; also elsewhere on the board

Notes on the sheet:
Src=0 —> Select ALU Result Src=1 —> Select Store Operand

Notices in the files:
PrototypeProcessor/MEMModuleTestFixture/MEMModuleTestFixture.kicad_pcb:
Copyright © 2023
RegisterFileModule/RegisterFileModule.kicad_pcb:
Copyright © 2022-2023 Andrew Fox
